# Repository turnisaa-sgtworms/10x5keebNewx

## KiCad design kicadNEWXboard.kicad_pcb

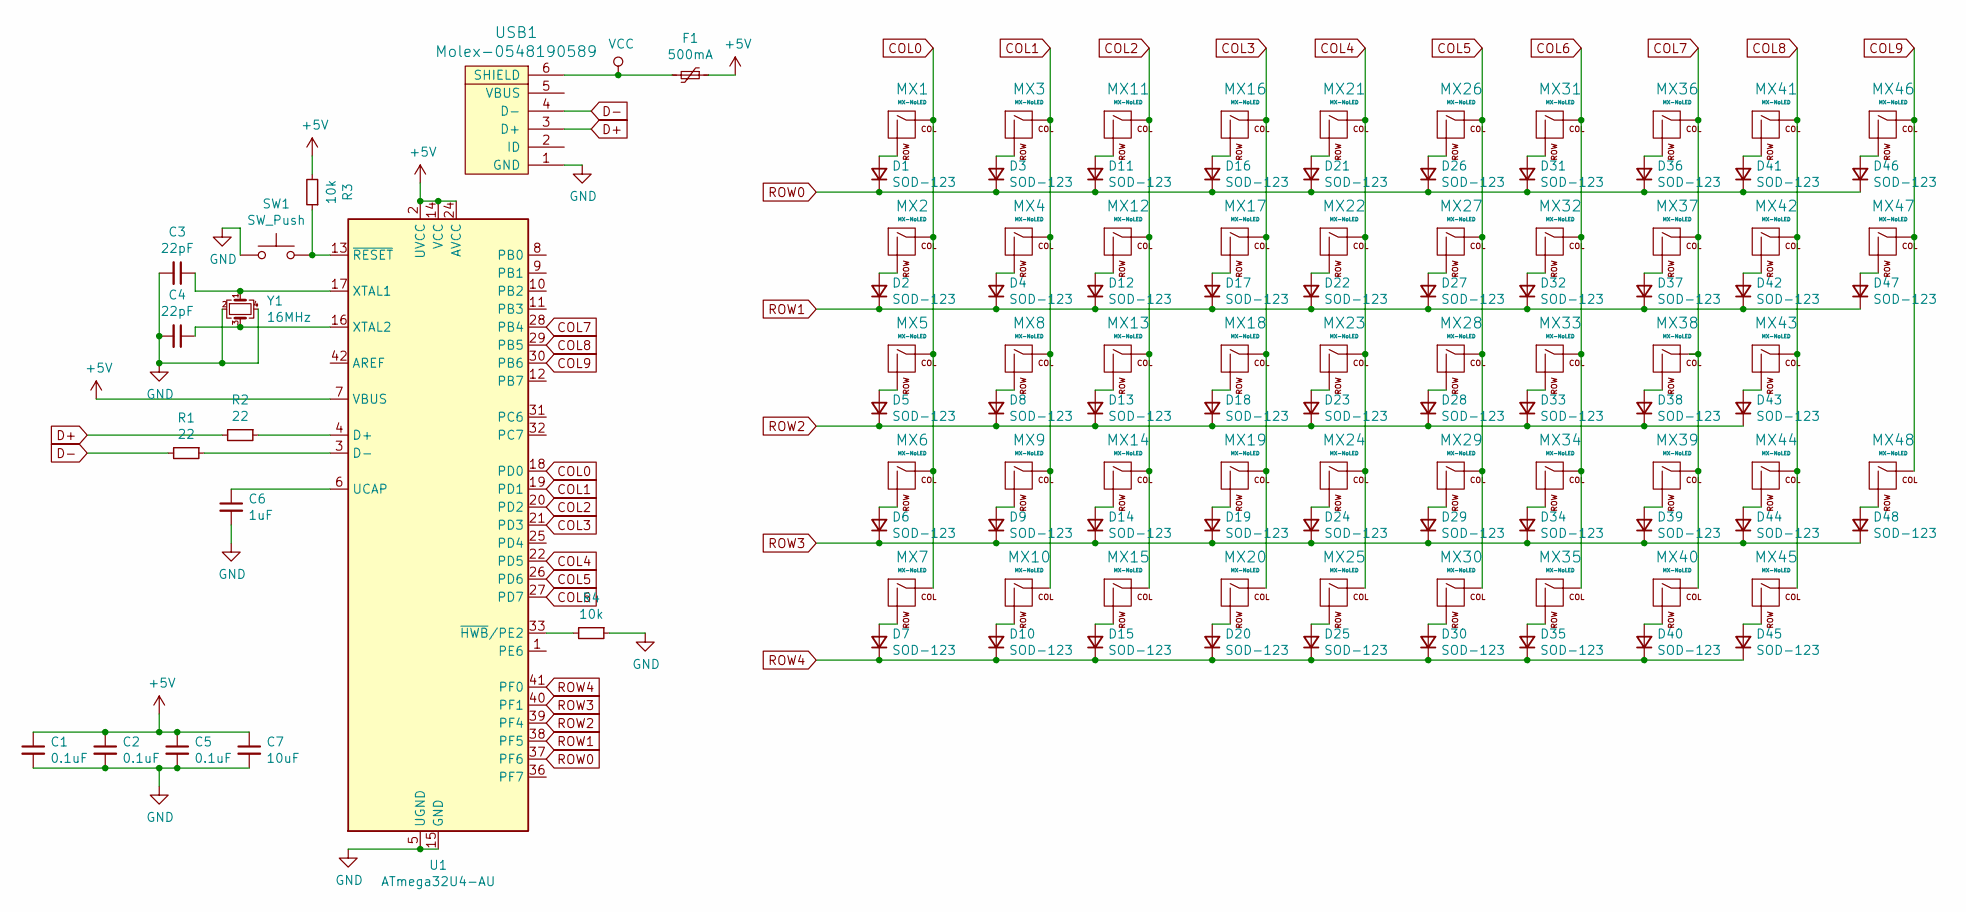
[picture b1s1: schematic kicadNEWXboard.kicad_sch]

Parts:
C1, C2, C5: 0.1uF; C_0805_2012Metric
C3, C4: 22pF; C_0805_2012Metric
C6: 1uF; C_0805_2012Metric
C7: 10uF; C_0805_2012Metric
D1, D2, D3, D4, D5, D6, D7, D8, D9, D10, D11, D12, D13, D14, D15, D16, D17, D18, D19, D20, D21, D22, D23, D24, D25, D26, D27, D28, D29, D30, D31, D32, D33, D34, D35, D36, D37, D38, D39, D40, D41, D42, D43, D44, D45, D46, D47, D48: SOD-123; D_SOD-123
F1: 500mA; Fuse_1206_3216Metric
MX1, MX2, MX3, MX4, MX5, MX6, MX7, MX8, MX9, MX10, MX11, MX12, MX13, MX14, MX15, MX16, MX17, MX18, MX19, MX20, MX21, MX22, MX23, MX24, MX25, MX26, MX27, MX28, MX29, MX30, MX31, MX32, MX33, MX34, MX35, MX36, MX37, MX38, MX39, MX40, MX41, MX42, MX43, MX44, MX45, MX46, MX47, MX48: MX-NoLED; MX-1U
R1, R2: 22; R_0805_2012Metric
R3, R4: 10k; R_0805_2012Metric
SW1: SW_Push; SKQG-1155865
U1: ATmega32U4-AU; TQFP-44_10x10mm_P0.8mm
USB1: Molex-0548190589; Molex-0548190519
Y1: 16MHz; Crystal_SMD_3225-4Pin_3.2x2.5mm

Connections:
+5V: C1.1, C2.1, C5.1, C7.1, F1.1, R3.2, U1.2 (UVCC), U1.7 (VBUS), U1.14 (VCC), U1.24 (AVCC), U1.34 (VCC), U1.44 (AVCC)
COL0: MX1.1 (COL), MX2.1 (COL), MX5.1 (COL), MX6.1 (COL), MX7.1 (COL), U1.18 (PD0)
COL1: MX3.1 (COL), MX4.1 (COL), MX8.1 (COL), MX9.1 (COL), MX10.1 (COL), U1.19 (PD1)
COL2: MX11.1 (COL), MX12.1 (COL), MX13.1 (COL), MX14.1 (COL), MX15.1 (COL), U1.20 (PD2)
COL3: MX16.1 (COL), MX17.1 (COL), MX18.1 (COL), MX19.1 (COL), MX20.1 (COL), U1.21 (PD3)
COL4: MX21.1 (COL), MX22.1 (COL), MX23.1 (COL), MX24.1 (COL), MX25.1 (COL), U1.22 (PD5)
COL5: MX26.1 (COL), MX27.1 (COL), MX28.1 (COL), MX29.1 (COL), MX30.1 (COL), U1.26 (PD6)
COL6: MX31.1 (COL), MX32.1 (COL), MX33.1 (COL), MX34.1 (COL), MX35.1 (COL), U1.27 (PD7)
COL7: MX36.1 (COL), MX37.1 (COL), MX38.1 (COL), MX39.1 (COL), MX40.1 (COL), U1.28 (PB4)
COL8: MX41.1 (COL), MX42.1 (COL), MX43.1 (COL), MX44.1 (COL), MX45.1 (COL), U1.29 (PB5)
COL9: MX46.1 (COL), MX47.1 (COL), MX48.1 (COL), U1.30 (PB6)
D+: R2.2, USB1.3 (D+)
D-: R1.2, USB1.4 (D-)
GND: C1.2, C2.2, C3.2, C4.2, C5.2, C6.2, C7.2, R4.1, SW1.1, U1.5 (UGND), U1.15 (GND), U1.23 (GND), U1.35 (GND), U1.43 (GND), USB1.1 (GND), Y1.2, Y1.4
unnamed: C3.1, U1.17 (XTAL1), Y1.1
unnamed: C4.1, U1.16 (XTAL2), Y1.3
unnamed: C6.1, U1.6 (UCAP)
unnamed: D1.2 (A), MX1.2 (ROW)
unnamed: D2.2 (A), MX2.2 (ROW)
unnamed: D3.2 (A), MX3.2 (ROW)
unnamed: D4.2 (A), MX4.2 (ROW)
unnamed: D5.2 (A), MX5.2 (ROW)
unnamed: D6.2 (A), MX6.2 (ROW)
unnamed: D7.2 (A), MX7.2 (ROW)
unnamed: D8.2 (A), MX8.2 (ROW)
unnamed: D9.2 (A), MX9.2 (ROW)
unnamed: D10.2 (A), MX10.2 (ROW)
unnamed: D11.2 (A), MX11.2 (ROW)
unnamed: D12.2 (A), MX12.2 (ROW)
unnamed: D13.2 (A), MX13.2 (ROW)
unnamed: D14.2 (A), MX14.2 (ROW)
unnamed: D15.2 (A), MX15.2 (ROW)
unnamed: D16.2 (A), MX16.2 (ROW)
unnamed: D17.2 (A), MX17.2 (ROW)
unnamed: D18.2 (A), MX18.2 (ROW)
unnamed: D19.2 (A), MX19.2 (ROW)
unnamed: D20.2 (A), MX20.2 (ROW)
unnamed: D21.2 (A), MX21.2 (ROW)
unnamed: D22.2 (A), MX22.2 (ROW)
unnamed: D23.2 (A), MX23.2 (ROW)
unnamed: D24.2 (A), MX24.2 (ROW)
unnamed: D25.2 (A), MX25.2 (ROW)
unnamed: D26.2 (A), MX26.2 (ROW)
unnamed: D27.2 (A), MX27.2 (ROW)
unnamed: D28.2 (A), MX28.2 (ROW)
unnamed: D29.2 (A), MX29.2 (ROW)
unnamed: D30.2 (A), MX30.2 (ROW)
unnamed: D31.2 (A), MX31.2 (ROW)
unnamed: D32.2 (A), MX32.2 (ROW)
unnamed: D33.2 (A), MX33.2 (ROW)
unnamed: D34.2 (A), MX34.2 (ROW)
unnamed: D35.2 (A), MX35.2 (ROW)
unnamed: D36.2 (A), MX36.2 (ROW)
unnamed: D37.2 (A), MX37.2 (ROW)
unnamed: D38.2 (A), MX38.2 (ROW)
unnamed: D39.2 (A), MX39.2 (ROW)
unnamed: D40.2 (A), MX40.2 (ROW)
unnamed: D41.2 (A), MX41.2 (ROW)
unnamed: D42.2 (A), MX42.2 (ROW)
unnamed: D43.2 (A), MX43.2 (ROW)
unnamed: D44.2 (A), MX44.2 (ROW)
unnamed: D45.2 (A), MX45.2 (ROW)
unnamed: D46.2 (A), MX46.2 (ROW)
unnamed: D47.2 (A), MX47.2 (ROW)
unnamed: D48.2 (A), MX48.2 (ROW)
unnamed: R1.1, U1.3 (D-)
unnamed: R2.1, U1.4 (D+)
unnamed: R3.1, SW1.2, U1.13 (~RESET)
unnamed: R4.2, U1.33 (~HWB/PE2)
ROW0: D1.1 (K), D3.1 (K), D11.1 (K), D16.1 (K), D21.1 (K), D26.1 (K), D31.1 (K), D36.1 (K), D41.1 (K), D46.1 (K), U1.37 (PF6)
ROW1: D2.1 (K), D4.1 (K), D12.1 (K), D17.1 (K), D22.1 (K), D27.1 (K), D32.1 (K), D37.1 (K), D42.1 (K), D47.1 (K), U1.38 (PF5)
ROW2: D5.1 (K), D8.1 (K), D13.1 (K), D18.1 (K), D23.1 (K), D28.1 (K), D33.1 (K), D38.1 (K), D43.1 (K), U1.39 (PF4)
ROW3: D6.1 (K), D9.1 (K), D14.1 (K), D19.1 (K), D24.1 (K), D29.1 (K), D34.1 (K), D39.1 (K), D44.1 (K), D48.1 (K), U1.40 (PF1)
ROW4: D7.1 (K), D10.1 (K), D15.1 (K), D20.1 (K), D25.1 (K), D30.1 (K), D35.1 (K), D40.1 (K), D45.1 (K), U1.41 (PF0)
VCC: F1.2, USB1.6 (SHIELD)

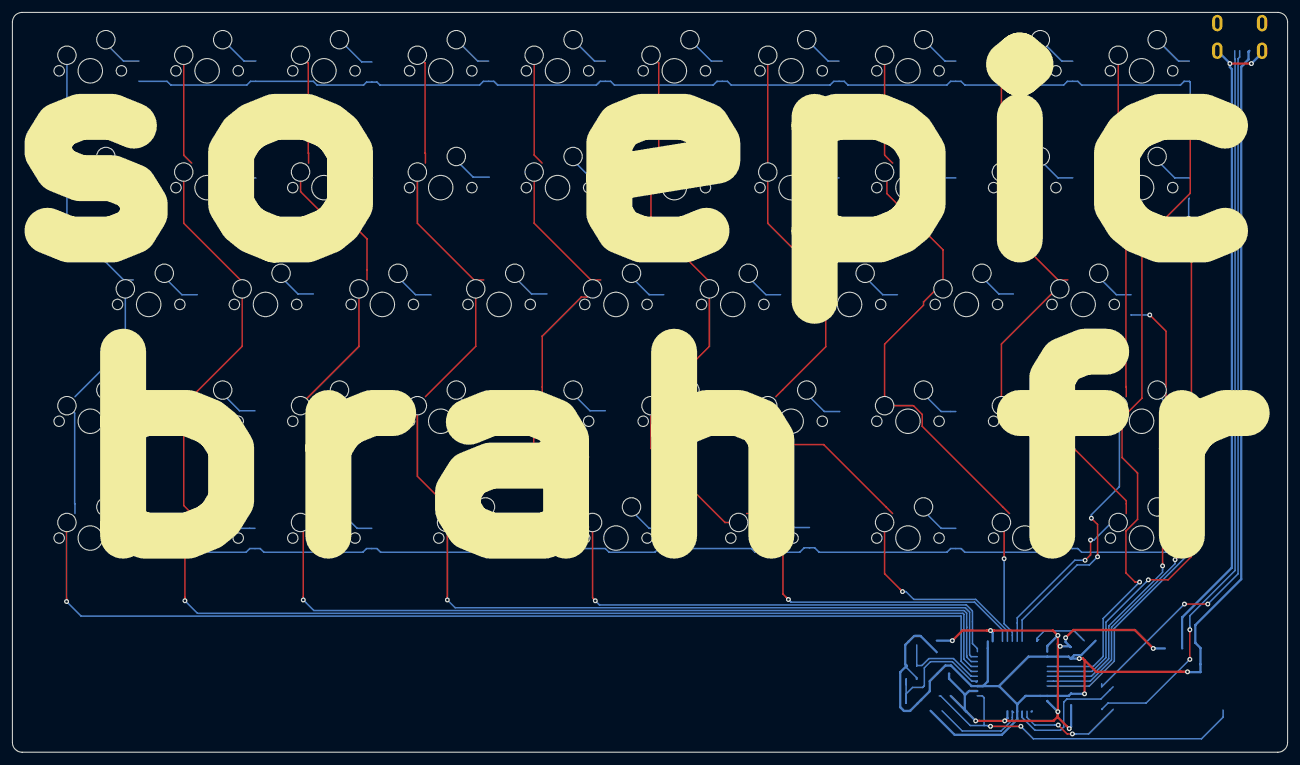
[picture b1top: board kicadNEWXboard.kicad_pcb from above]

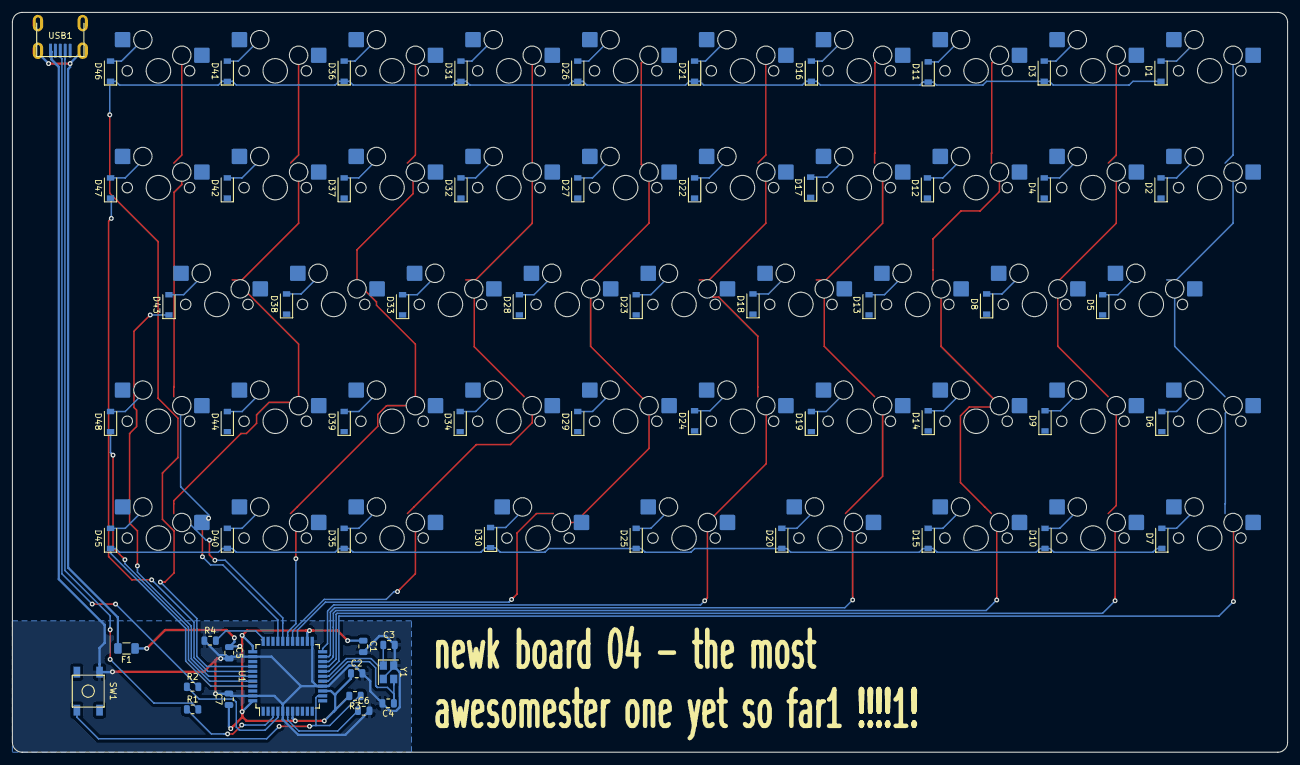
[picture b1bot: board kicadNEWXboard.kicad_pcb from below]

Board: 2 copper layers, 208.0 x 120.7 mm, 112 parts (64 on the bottom side), 75 nets.

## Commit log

2024-11-13 uploaded beginning steps
    Uploaded the first steps creating keeb
2024-11-13 updated layout
2024-11-13 created kicad files
2024-11-13 added submodules
2024-11-13 added .pretty and .lib(s)
2024-11-13 schematic work
    finished crystal
    https://wiki.ai03.com/books/pcb-design/page/pcb-guide-part-3---creating-the-mcu-schematic
    continue at: The reset button is pressed to...
2024-11-13 schematic and footprints bound
2024-11-13 routing
    last at: Step "10. Choosing the matrix pinout"
2024-11-14 gerbers hooray
2024-11-14 slimming electronics
2024-11-15 added hotswap submod
2024-11-15 added .pretty(s)
2024-11-15 removed unneeded pretty
2024-11-15 added submodule marbastlib
2024-11-15 push before updating kicad vers
2024-11-15 lots of stuff
    updated to new KiCad version
